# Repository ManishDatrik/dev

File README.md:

# DEVBOD PCB Design

A PCB design project created using **KiCad** to learn the complete hardware design workflow, from schematic creation to PCB layout and manufacturing file generation.

---

## About

This project was designed in KiCad as part of my learning in PCB design. It includes creating the schematic, assigning footprints, designing the PCB layout, routing the connections, checking the design for errors, and generating the manufacturing files.

---
## Travel Purpose

Portable electronic devices have become an important part of travelling. A compact PCB like DEVBOD can serve as the foundation for travel-related embedded systems such as:

- Smart travel accessories
- Portable communication devices
- IoT-based travel gadgets
- Compact wireless hardware
- Outdoor and trekking electronics

This project demonstrates how PCB design can be applied to build small, portable hardware solutions for travel applications.

---
## Tools Used

- KiCad

---

## Project Workflow

- Created the schematic
- Connected the required components
- Assigned footprints
- Designed the PCB layout
- Routed the PCB traces
- Performed Design Rule Check (DRC)
- Generated Gerber files for PCB manufacturing

---

## Project Files

```
DEVBOD.kicad_sch
DEVBOD.kicad_pcb
DEVBOD.kicad_pro
DEVBOD.kicad_prl

DEVBOD-F_Cu.gbr
DEVBOD-B_Cu.gbr
DEVBOD-F_Mask.gbr
DEVBOD-B_Mask.gbr
DEVBOD-F_Paste.gbr
DEVBOD-B_Paste.gbr
DEVBOD-F_Silkscreen.gbr
DEVBOD-B_Silkscreen.gbr
DEVBOD-Edge_Cuts.gbr

DEVBOD-job.gbrjob
```

---

## What I Learned

- Schematic design in KiCad
- PCB layout and routing
- Footprint assignment
- Design Rule Check (DRC)
- Gerber file generation
- Basic PCB design workflow

---

## Project Preview
- Schematic
- PCB Layout
- 3D View 
- Manufactured PCB (if available)

---

This project was built for learning and improving my PCB design skills using KiCad.
https://github.com/ManishDatrik/dev.git

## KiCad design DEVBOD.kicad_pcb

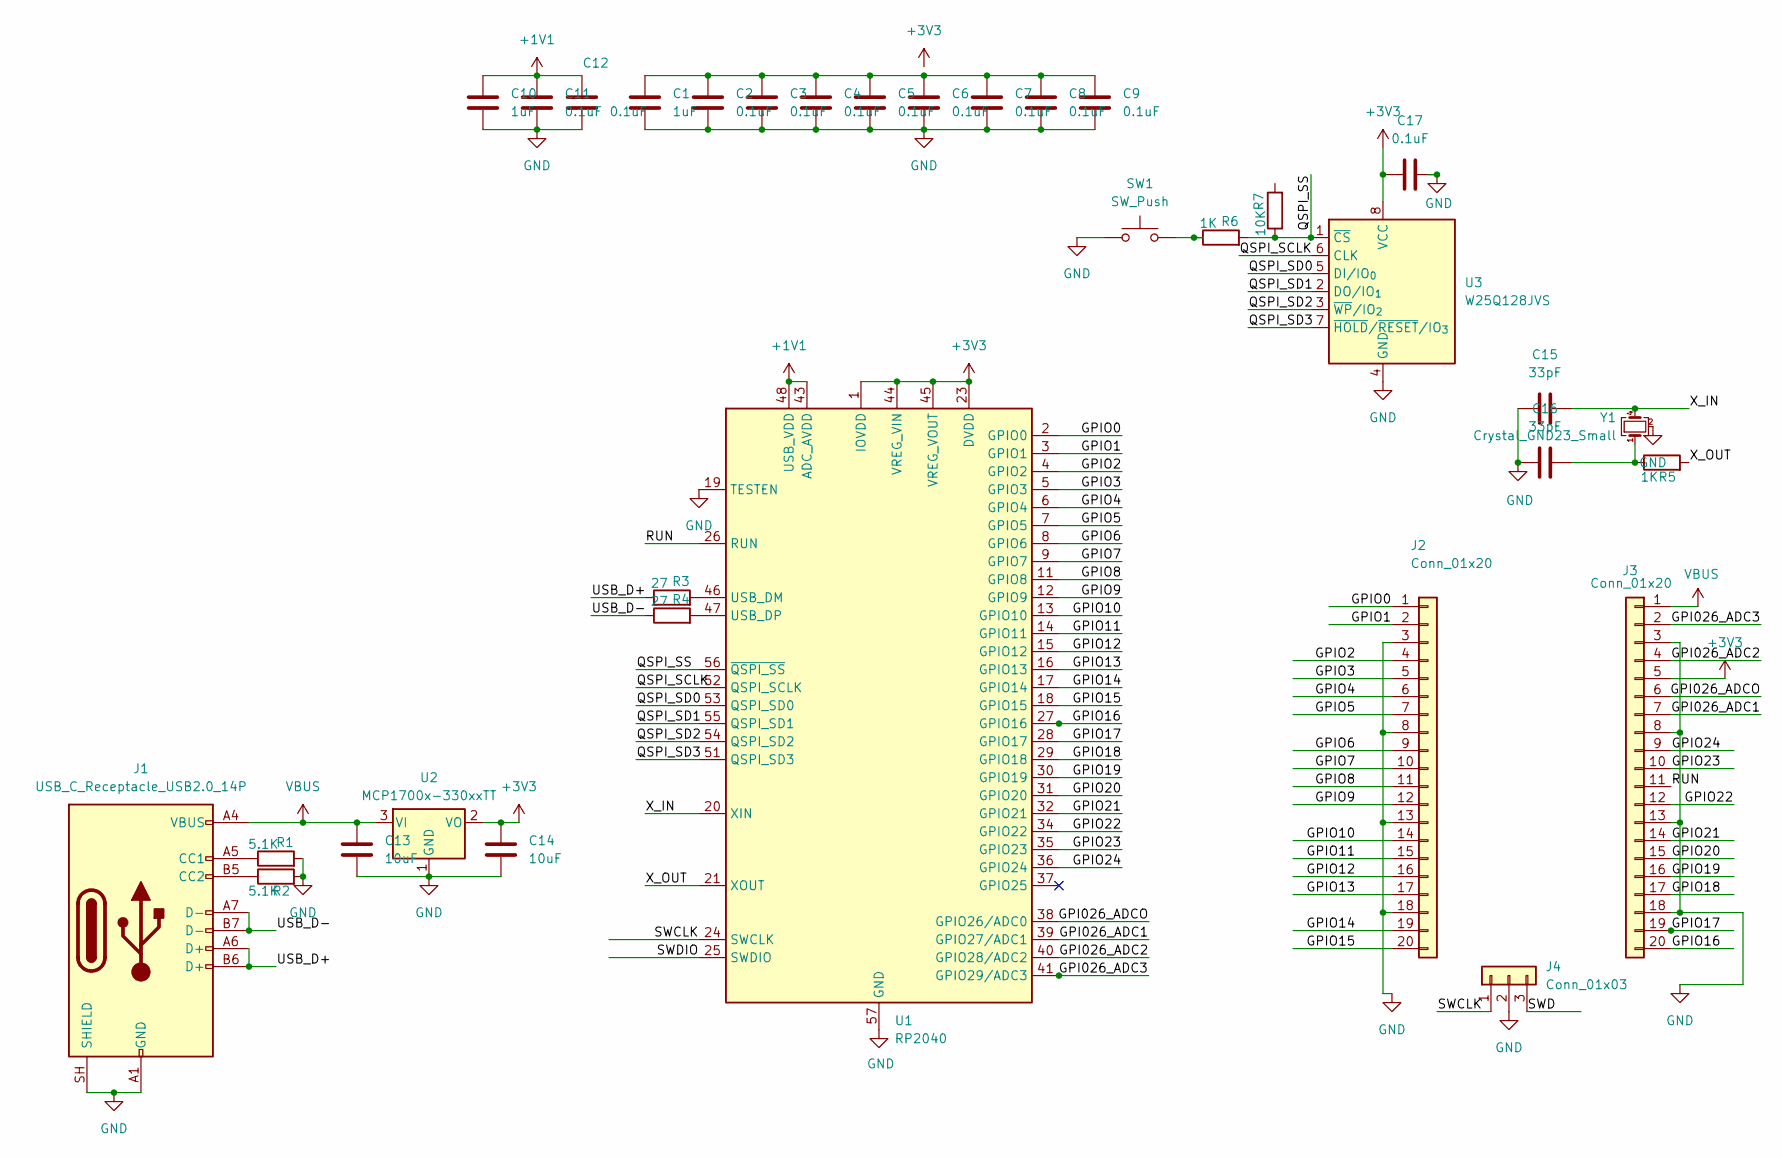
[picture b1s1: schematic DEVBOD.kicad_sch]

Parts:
C1, C10: 1uF; C_0402_1005Metric
C2, C3, C4, C5, C6, C7, C8, C9, C11, C12, C17: 0.1uF; C_0402_1005Metric
C13, C14: 10uF; C_0603_1608Metric
C15, C16: 33pF; C_0402_1005Metric
J1: USB_C_Receptacle_USB2.0_14P; USB_C_Receptacle_HRO_TYPE-C-31-M-12
J2, J3: Conn_01x20; PinHeader_1x20_P2.54mm_Vertical
J4: Conn_01x03; PinHeader_1x03_P2.54mm_Vertical
R1, R2: 5.1K; R_0402_1005Metric
R3, R4: 27; R_0402_1005Metric
R5, R6: 1K; R_0402_1005Metric
R7: 10K; R_0402_1005Metric
SW1: SW_Push; SW_Push_SPST_NO_Alps_SKRK
U1: RP2040; QFN-56-1EP_7x7mm_P0.4mm_EP3.2x3.2mm
U2: MCP1700x-330xxTT; SOT-23
U3: W25Q128JVS; Winbond_USON-8-1EP_3x2mm_P0.5mm_EP0.2x1.6mm
Y1: Crystal_GND23_Small; Crystal_SMD_3225-4Pin_3.2x2.5mm

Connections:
+1V1: C10.1, C11.1, C12.1, U1.43 (ADC_AVDD), U1.48 (USB_VDD)
+3V3: C14.1, C17.1, J3.5, U1.1 (IOVDD), U1.10 (IOVDD), U1.22 (IOVDD), U1.23 (DVDD), U1.33 (IOVDD), U1.42 (IOVDD), U1.44 (VREG_VIN), U1.45 (VREG_VOUT), U1.49 (IOVDD), U1.50 (DVDD), U2.2 (VO), U3.8 (VCC)
/GPI026_ADC1: J3.7, U1.39 (GPIO27/ADC1)
/GPI026_ADC2: J3.4, U1.40 (GPIO28/ADC2)
/GPI026_ADC3: U1.41 (GPIO29/ADC3)
/GPI026_ADCO: J3.6, U1.38 (GPIO26/ADC0)
/GPIO0: J2.1, U1.2 (GPIO0)
/GPIO1: J2.2, U1.3 (GPIO1)
/GPIO2: J2.4, U1.4 (GPIO2)
/GPIO3: J2.5, U1.5 (GPIO3)
/GPIO4: J2.6, U1.6 (GPIO4)
/GPIO5: J2.7, U1.7 (GPIO5)
/GPIO6: J2.9, U1.8 (GPIO6)
/GPIO7: J2.10, U1.9 (GPIO7)
/GPIO8: J2.11, U1.11 (GPIO8)
/GPIO9: J2.12, U1.12 (GPIO9)
/GPIO10: J2.14, U1.13 (GPIO10)
/GPIO11: J2.15, U1.14 (GPIO11)
/GPIO12: J2.16, U1.15 (GPIO12)
/GPIO13: J2.17, U1.16 (GPIO13)
/GPIO14: J2.19, U1.17 (GPIO14)
/GPIO15: J2.20, U1.18 (GPIO15)
/GPIO16: J3.20, U1.27 (GPIO16)
/GPIO17: J3.19, U1.28 (GPIO17)
/GPIO18: J3.17, U1.29 (GPIO18)
/GPIO19: J3.16, U1.30 (GPIO19)
/GPIO20: J3.15, U1.31 (GPIO20)
/GPIO21: J3.14, U1.32 (GPIO21)
/GPIO22: J3.12, U1.34 (GPIO22)
/GPIO23: J3.10, U1.35 (GPIO23)
/GPIO24: J3.9, U1.36 (GPIO24)
/QSPI_SCLK: U1.52 (QSPI_SCLK), U3.6 (CLK)
/QSPI_SD0: U1.53 (QSPI_SD0), U3.5 (DI/IO_{0})
/QSPI_SD1: U1.55 (QSPI_SD1), U3.2 (DO/IO_{1})
/QSPI_SD2: U1.54 (QSPI_SD2), U3.3 (~WP/IO_{2})
/QSPI_SD3: U1.51 (QSPI_SD3), U3.7 (~HOLD/~RESET/IO_{3})
/QSPI_SS: R6.2, R7.1, U1.56 (~QSPI_SS), U3.1 (~CS)
/RUN: J3.11, U1.26 (RUN)
/SWCLK: J4.1, U1.24 (SWCLK)
/SWD: J4.3
/SWDIO: U1.25 (SWDIO)
/USB_D+: J1.A6 (D+), J1.B6 (D+), R3.1
/USB_D-: J1.A7 (D-), J1.B7 (D-), R4.1
/X_IN: C15.2, U1.20 (XIN), Y1.4
/X_OUT: R5.2, U1.21 (XOUT)
GND: C1.2, C2.2, C3.2, C4.2, C5.2, C6.2, C7.2, C8.2, C9.2, C10.2, C11.2, C12.2, C13.2, C14.2, C15.1, C16.1, C17.2, J1.A1 (GND), J1.A12 (GND), J1.B1 (GND), J1.B12 (GND), J1.SH (SHIELD), J2.3, J2.8, J2.13, J2.18, J3.3, J3.8, J3.13, J3.18, J4.2, R1.2, R2.2, SW1.1, U1.19 (TESTEN), U1.57 (GND), U2.1 (GND), U3.4 (GND), Y1.2 (G), Y1.3 (G)
unnamed: C1.1, C2.1, C3.1, C4.1, C5.1, C6.1, C7.1, C8.1, C9.1
unnamed: C16.2, R5.1, Y1.1
unnamed: J1.A5 (CC1), R1.1
unnamed: J1.B5 (CC2), R2.1
unnamed: R6.1, SW1.2
unnamed: R3.2, U1.46 (USB_DM)
unnamed: R4.2, U1.47 (USB_DP)
VBUS: C13.1, J1.A4 (VBUS), J1.A9 (VBUS), J1.B4 (VBUS), J1.B9 (VBUS), J3.1, U2.3 (VI)

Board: 2 copper layers, 33 parts (0 on the bottom side), 51 nets, no tracks yet.
